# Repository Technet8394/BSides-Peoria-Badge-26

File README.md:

# BSides-Peoria-Badge-26
The badge schematic and board design for the BSides Peoria. Super cool thing I got to do.

## Technical Details and notes for nerds

I spent around a month and a half working on this badge, not because of procrastination, but that's when I found out I was doing it. I had some experience designing electronics projects before (see [Technet8394/HackTheBadge](https://github.com/Technet8394/HackTheBadge)) but had never designed a PCB before. I ended up throwing myself off the deep end with this one.

I have put a picture of the board programmer I fabricated in an hour using Pogo pins and JST Jumper wiring, (side note, yes I did solder directly to the ends of said jumper wires). It ended up working perfectly on every single one of the 300 boards I programmed. Unboxing, programming and repackaging actually only took an hour and a half. The programming script was lost due to my WSL instance destroying its virtual disk beyond repair. Which is wildly unfortunate, but beyond my control. 

The board was made with love in KiCAD, gotta love KiCAD, anywho if you have any questions DM me at technet.1337 on signal.

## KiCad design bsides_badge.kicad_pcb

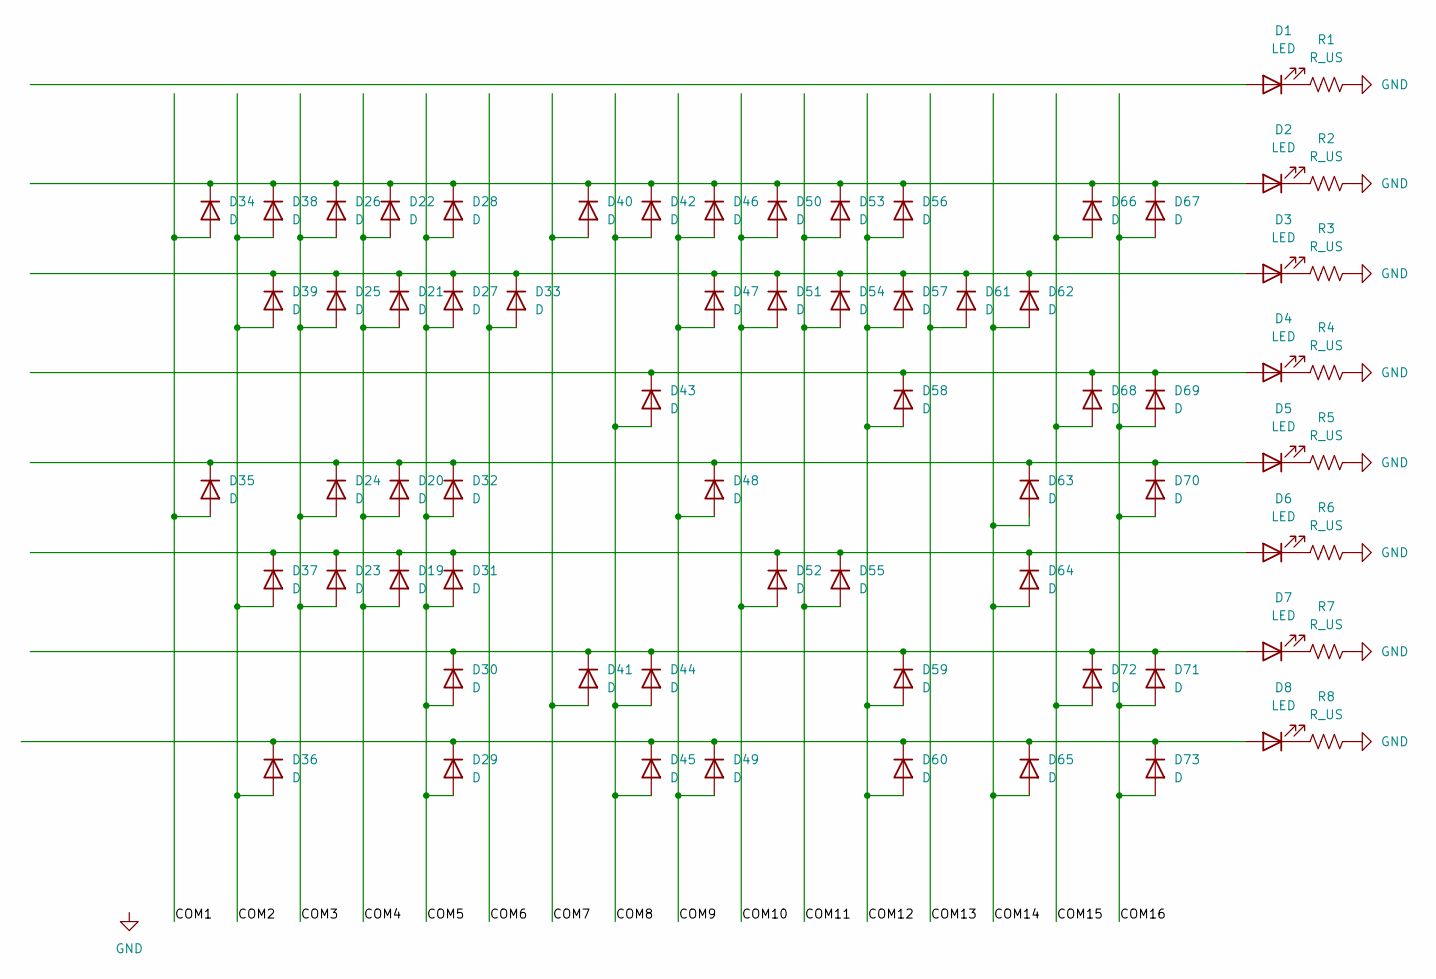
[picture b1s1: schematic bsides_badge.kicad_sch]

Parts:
D1, D2, D3, D4, D5, D6, D7, D8: LED; LED_0805_2012Metric; JLCPCB ID# C84256
D19, D20, D21, D22, D23, D24, D25, D26, D27, D28, D29, D30, D31, D32, D33, D34, D35, D36, D37, D38, D39, D40, D41, D42, D43, D44, D45, D46, D47, D48, D49, D50, D51, D52, D53, D54, D55, D56, D57, D58, D59, D60, D61, D62, D63, D64, D65, D66, D67, D68, D69, D70, D71, D72, D73: D; D_0805_2012Metric; JLCPCB ID# C2128
R1, R2, R3, R4, R5, R6, R7, R8: R_US; R_0805_2012Metric; JLCPCB ID# C17513

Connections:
/COM1: D34.2 (A), D35.2 (A)
/COM2: D36.2 (A), D37.2 (A), D38.2 (A), D39.2 (A)
/COM3: D23.2 (A), D24.2 (A), D25.2 (A), D26.2 (A)
/COM4: D19.2 (A), D20.2 (A), D21.2 (A), D22.2 (A)
/COM5: D27.2 (A), D28.2 (A), D29.2 (A), D30.2 (A), D31.2 (A), D32.2 (A)
/COM6: D33.2 (A)
/COM7: D40.2 (A), D41.2 (A)
/COM8: D42.2 (A), D43.2 (A), D44.2 (A), D45.2 (A)
/COM9: D46.2 (A), D47.2 (A), D48.2 (A), D49.2 (A)
/COM10: D50.2 (A), D51.2 (A), D52.2 (A)
/COM11: D53.2 (A), D54.2 (A), D55.2 (A)
/COM12: D56.2 (A), D57.2 (A), D58.2 (A), D59.2 (A), D60.2 (A)
/COM13: D61.2 (A)
/COM14: D62.2 (A), D63.2 (A), D64.2 (A), D65.2 (A)
/COM15: D66.2 (A), D68.2 (A), D72.2 (A)
/COM16: D67.2 (A), D69.2 (A), D70.2 (A), D71.2 (A), D73.2 (A)
GND: R1.1, R2.1, R3.1, R4.1, R5.1, R6.1, R7.1, R8.1; also elsewhere on the board
unnamed 17: D1.1 (K), R1.2; also elsewhere on the board
unnamed: D2.2 (A), D22.1 (K), D26.1 (K), D28.1 (K), D34.1 (K), D38.1 (K), D40.1 (K), D42.1 (K), D46.1 (K), D50.1 (K), D53.1 (K), D56.1 (K), D66.1 (K), D67.1 (K)
unnamed: D2.1 (K), R2.2
unnamed: D3.1 (K), R3.2
unnamed: D4.2 (A), D43.1 (K), D58.1 (K), D68.1 (K), D69.1 (K)
unnamed: D4.1 (K), R4.2
unnamed: D5.1 (K), R5.2
unnamed: D6.1 (K), R6.2
unnamed: D7.1 (K), R7.2
unnamed: D8.1 (K), R8.2
unnamed: D6.2 (A), D19.1 (K), D23.1 (K), D31.1 (K), D37.1 (K), D52.1 (K), D55.1 (K), D64.1 (K)
unnamed: D5.2 (A), D20.1 (K), D24.1 (K), D32.1 (K), D35.1 (K), D48.1 (K), D63.1 (K), D70.1 (K)
unnamed: D3.2 (A), D21.1 (K), D25.1 (K), D27.1 (K), D33.1 (K), D39.1 (K), D47.1 (K), D51.1 (K), D54.1 (K), D57.1 (K), D61.1 (K), D62.1 (K)
unnamed: D8.2 (A), D29.1 (K), D36.1 (K), D45.1 (K), D49.1 (K), D60.1 (K), D65.1 (K), D73.1 (K)
unnamed: D7.2 (A), D30.1 (K), D41.1 (K), D44.1 (K), D59.1 (K), D71.1 (K), D72.1 (K)

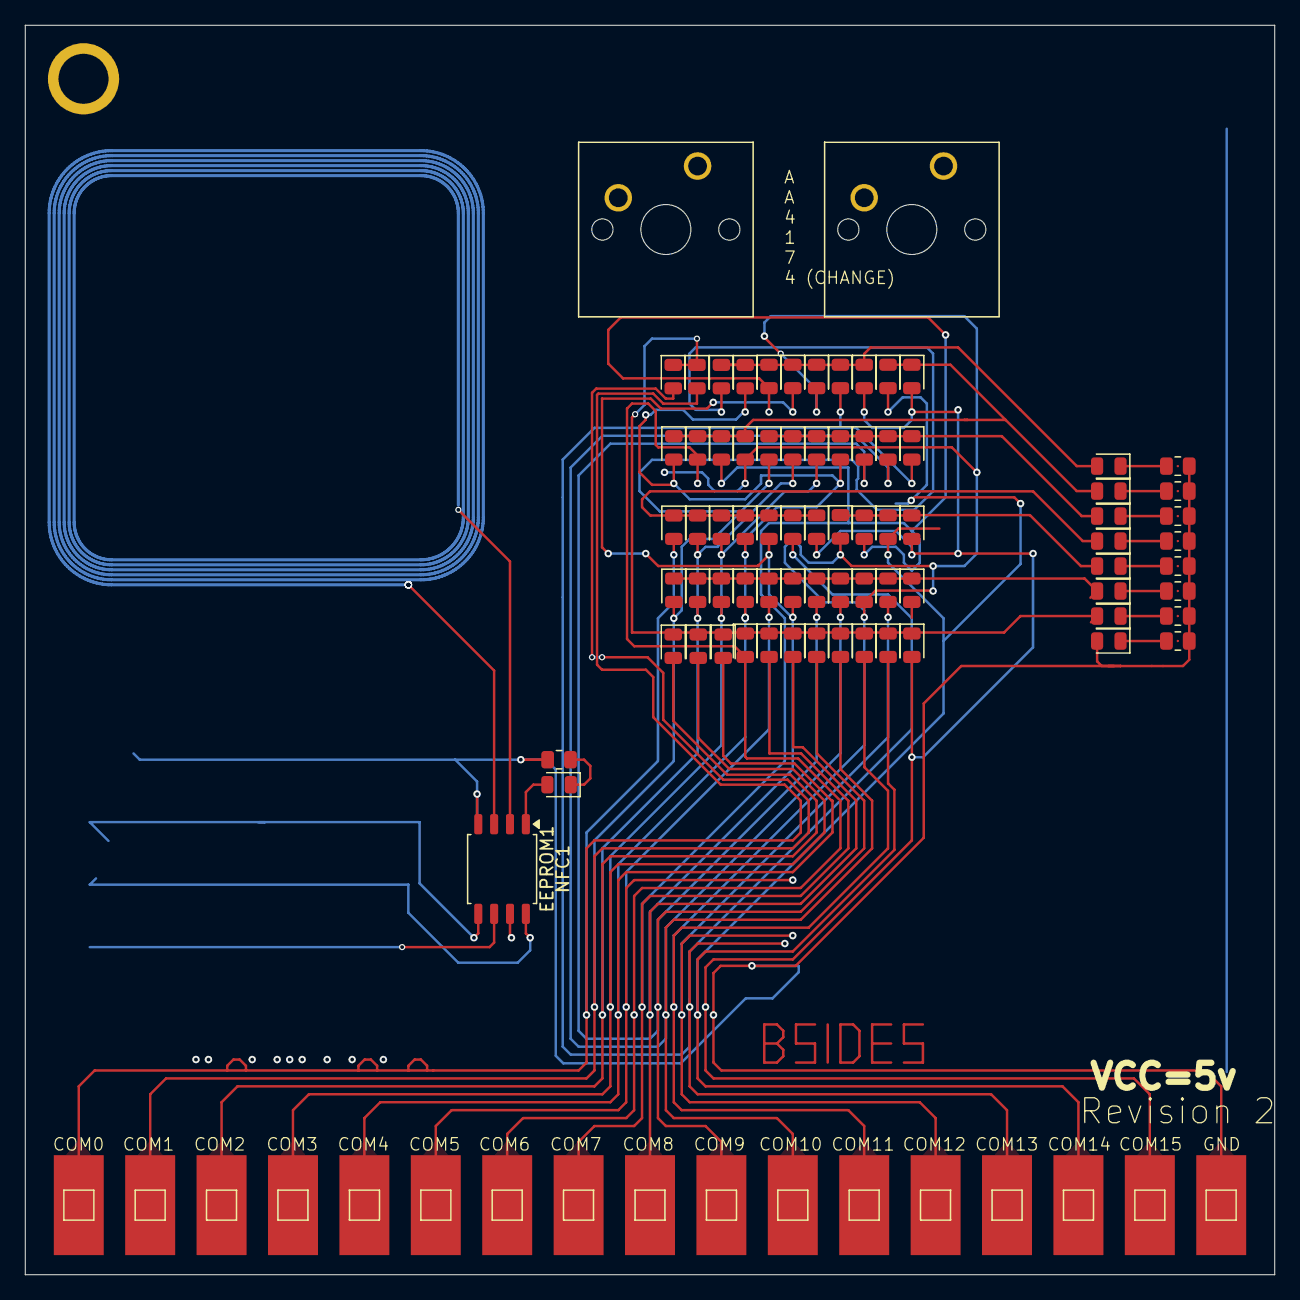
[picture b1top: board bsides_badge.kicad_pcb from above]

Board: 2 copper layers, 100.0 x 100.0 mm, 75 parts (1 on the bottom side), 30 nets.

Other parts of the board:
D1#2: LED; LED_0805_2012Metric
D34#2: D; D_0805_2012Metric
NFC: NFC_35x35_N6_NXP_NTAG213_215_216
NFC1: SOIC-8_5.3x5.3mm_P1.27mm
R1#2: R_US; R_0805_2012Metric

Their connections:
GND: R1#2.1; also elsewhere on the board
unnamed 17: D1#2.1 (K_1); also elsewhere on the board

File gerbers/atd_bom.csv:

Designator,Footprint,Quantity,Value,LCSC Part #
"D1_2, D1, D2, D3, D4, D5, D6, D7, D8",0805,9,LED,
"D19, D20, D21, D22, D23, D24, D25, D26, D27, D28, D29, D30, D31, D32, D33, D34_2, D34, D35, D36, D37, D39, D40, D41, D42, D43, D44, D45, D46, D47, D48, D49, D50, D51, D52, D53, D54, D55, D56, D57, D58, D59, D60, D61, D62, D63, D64, D65, D66, D67, D68, D69, D70, D71, D72, D73",0805,55,D,
NFC,NFC_35x35_N6_NXP_NTAG213_215_216,1,NFC_35x35_N6_NXP_NTAG213_215_216,
NFC1,SOIC-8_3.9x4.9mm_P1.27mm,1,SOIC-8_3.9x4.9mm_P1.27mm,
"R1_2, R1, R2, R3, R4, R5, R6, R7, R8",0805,9,R_US,
